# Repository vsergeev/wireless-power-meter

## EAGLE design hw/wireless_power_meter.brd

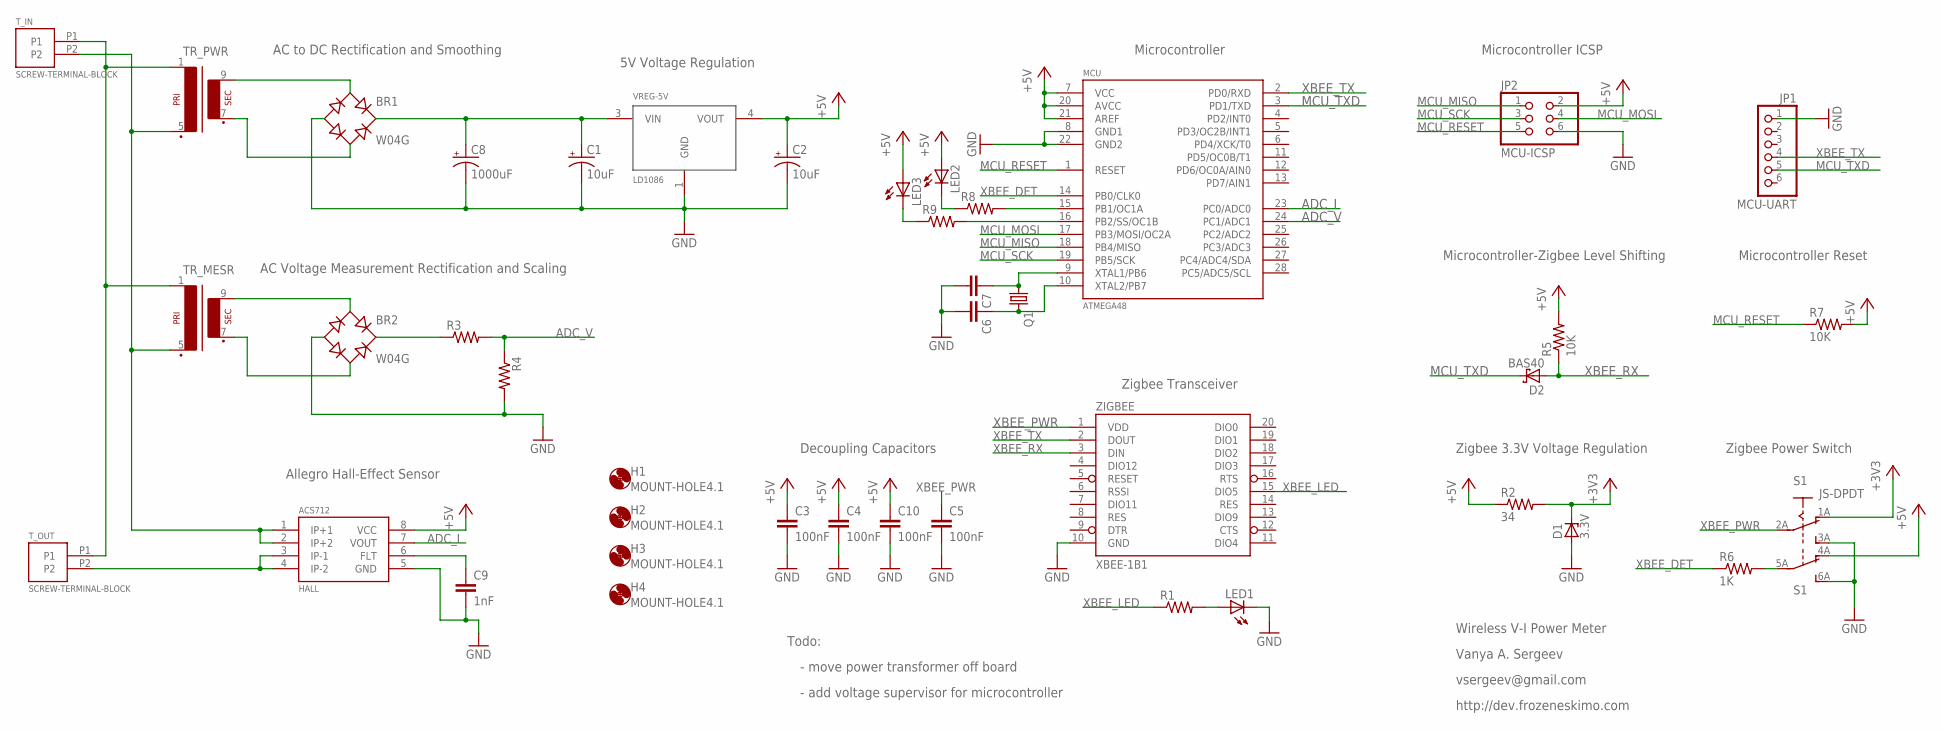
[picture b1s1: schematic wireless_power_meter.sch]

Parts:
BR1, BR2: W04G; WOG
C1, C2: 10uF; E2,5-5
C3, C4, C5, C10: 100nF; C0805
C6, C7: C-EUC0805; C0805
C8: 1000uF; E5-13
C9: 1nF; C0805
D1: 3.3V; SOT23
D2: BAS40; SOT23
H1, H2, H3, H4: MOUNT-HOLE4.1; 4,1
HALL: ACS712; SO8
JP1: MCU-UART; 1X06
JP2: MCU-ICSP; 2X03
LED1, LED2, LED3: LEDCHIPLED_0805; CHIPLED_0805
MCU: ATMEGA48; DIL28-3
Q1: CRYSTALTC26H; TC26H
R1, R3, R4, R8, R9: R-US_R0805; R0805
R2: 34; R0805
R5, R7: 10K; R0805
R6: 1K; R0805
S1: JS-DPDT; JS-MINI-SLIDE
TR_MESR: EI30-1
TR_PWR: EI30-1
T_IN: SCREW-TERMINAL-BLOCK; TERMINAL-BLOCK
T_OUT: SCREW-TERMINAL-BLOCK; TERMINAL-BLOCK
VREG-5V: LD1086; DPACK
ZIGBEE: XBEE-1B1; XBEE-1

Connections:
+3V3: D1.3 (C), R2.2, S1.1A (O)
+5V: C2.+, C3.1, C4.1, C10.1, HALL.8 (VCC), JP2.2, LED2.A, LED3.A, MCU.7 (VCC), MCU.20 (AVCC), MCU.21 (AREF), R2.1, R5.2, R7.2, S1.4A (O), VREG-5V.4 (VOUT)
ADC_I: HALL.7 (VOUT), MCU.23 (PC0/ADC0)
ADC_V: MCU.24 (PC1/ADC1), R3.2, R4.1
DC+: BR1.+, C1.+, C8.+, VREG-5V.3 (VIN)
GND: BR1.-, BR2.-, C1.-, C2.-, C3.2, C4.2, C5.2, C6.2, C7.2, C8.-, C9.2, C10.2, D1.1 (A), HALL.5 (GND), JP1.1, JP2.6, LED1.C, MCU.8 (GND1), MCU.22 (GND2), R4.2, S1.3A (S), S1.6A (S), VREG-5V.1 (GND), ZIGBEE.10 (GND)
MCU_MISO: JP2.1, MCU.18 (PB4/MISO)
MCU_MOSI: JP2.4, MCU.17 (PB3/MOSI/OC2A)
MCU_RESET: JP2.5, MCU.1 (RESET), R7.1
MCU_SCK: JP2.3, MCU.19 (PB5/SCK)
MCU_TXD: D2.3 (C), JP1.5, MCU.3 (PD1/TXD)
unnamed: BR1.AC1, TR_PWR.9 (S4)
unnamed: BR1.AC2, TR_PWR.7 (S3)
unnamed: C6.1, MCU.10 (XTAL2/PB7), Q1.2
unnamed: HALL.3 (IP-1), HALL.4 (IP-2), T_OUT.P2
unnamed: BR2.AC1, TR_MESR.9 (S4)
unnamed: BR2.AC2, TR_MESR.7 (S3)
unnamed: BR2.+, R3.1
unnamed: C9.1, HALL.6 (FLT)
unnamed: LED1.A, R1.2
unnamed: R6.2, S1.5A
unnamed: LED2.C, R8.1
unnamed: MCU.15 (PB1/OC1A), R8.2
unnamed: C7.1, MCU.9 (XTAL1/PB6), Q1.1
unnamed: MCU.16 (PB2/SS/OC1B), R9.2
unnamed: LED3.C, R9.1
unnamed: TR_MESR.1, TR_PWR.1, T_IN.P1, T_OUT.P1
unnamed: HALL.1 (IP+1), HALL.2 (IP+2), TR_MESR.5 (P2), TR_PWR.5 (P2), T_IN.P2
XBEE_DET: MCU.14 (PB0/CLK0), R6.1
XBEE_LED: R1.1, ZIGBEE.15 (DIO5)
XBEE_PWR: C5.1, S1.2A, ZIGBEE.1 (VDD)
XBEE_RX: D2.1 (A), R5.1, ZIGBEE.3 (DIN)
XBEE_TX: JP1.4, MCU.2 (PD0/RXD), ZIGBEE.2 (DOUT)

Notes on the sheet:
AC to DC Rectification and Smoothing
5V Voltage Regulation
AC Voltage Measurement Rectification and Scaling
Allegro Hall-Effect Sensor
Microcontroller
Zigbee Transceiver
Zigbee 3.3V Voltage Regulation
Decoupling Capacitors
Zigbee Power Switch
Microcontroller ICSP
Microcontroller-Zigbee Level Shifting
Microcontroller Reset
Wireless V-I Power Meter
Vanya A. Sergeev
vsergeev@gmail.com
http://dev.frozeneskimo.com
Todo:
- move power transformer off board
- add voltage supervisor for microcontroller

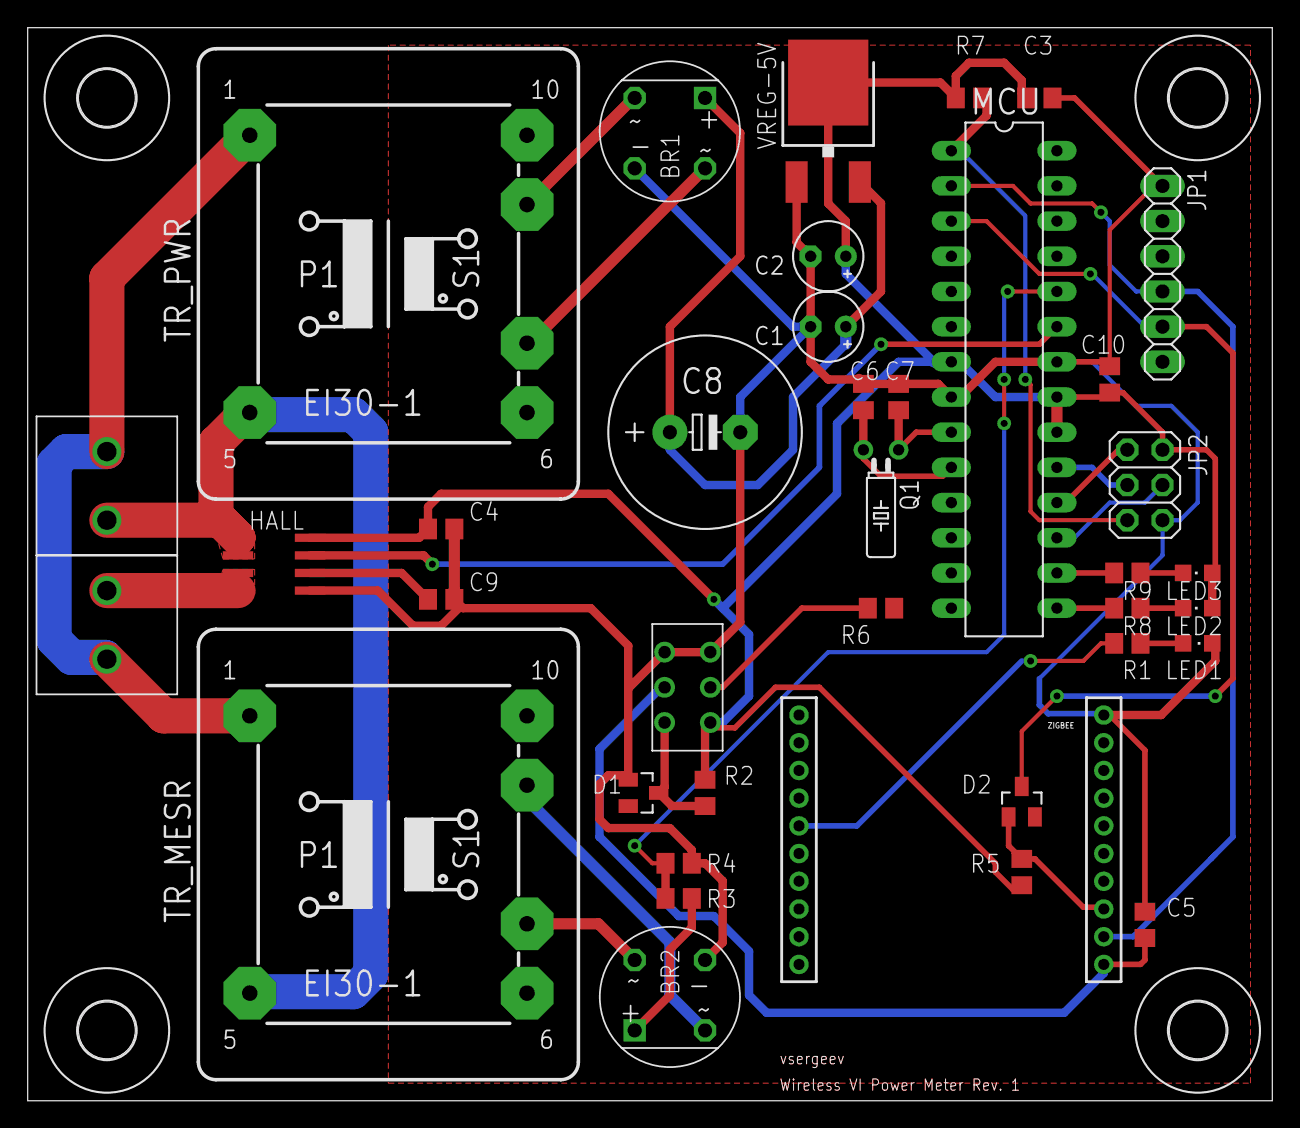
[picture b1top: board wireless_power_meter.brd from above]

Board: 2 copper layers, 89.8 x 77.5 mm, 42 parts (0 on the bottom side), 33 nets.

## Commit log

2012-03-06 updated board layout image with filled ground pour
